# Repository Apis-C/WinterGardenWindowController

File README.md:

## Welcome to GitHub Pages

You can use the [editor on GitHub](https://github.com/Apis-C/WinterGardenWindowController/edit/master/README.md) to maintain and preview the content for your website in Markdown files.

Whenever you commit to this repository, GitHub Pages will run [Jekyll](https://jekyllrb.com/) to rebuild the pages in your site, from the content in your Markdown files.

### Markdown

Markdown is a lightweight and easy-to-use syntax for styling your writing. It includes conventions for

```markdown
Syntax highlighted code block

# Header 1
## Header 2
### Header 3

- Bulleted
- List

1. Numbered
2. List

**Bold** and _Italic_ and `Code` text

[Link](url) and 
```

For more details see [GitHub Flavored Markdown](https://guides.github.com/features/mastering-markdown/).

### Jekyll Themes

Your Pages site will use the layout and styles from the Jekyll theme you have selected in your [repository settings](https://github.com/Apis-C/WinterGardenWindowController/settings). The name of this theme is saved in the Jekyll `_config.yml` configuration file.

### Support or Contact

Having trouble with Pages? Check out our [documentation](https://help.github.com/categories/github-pages-basics/) or [contact support](https://github.com/contact) and we’ll help you sort it out.

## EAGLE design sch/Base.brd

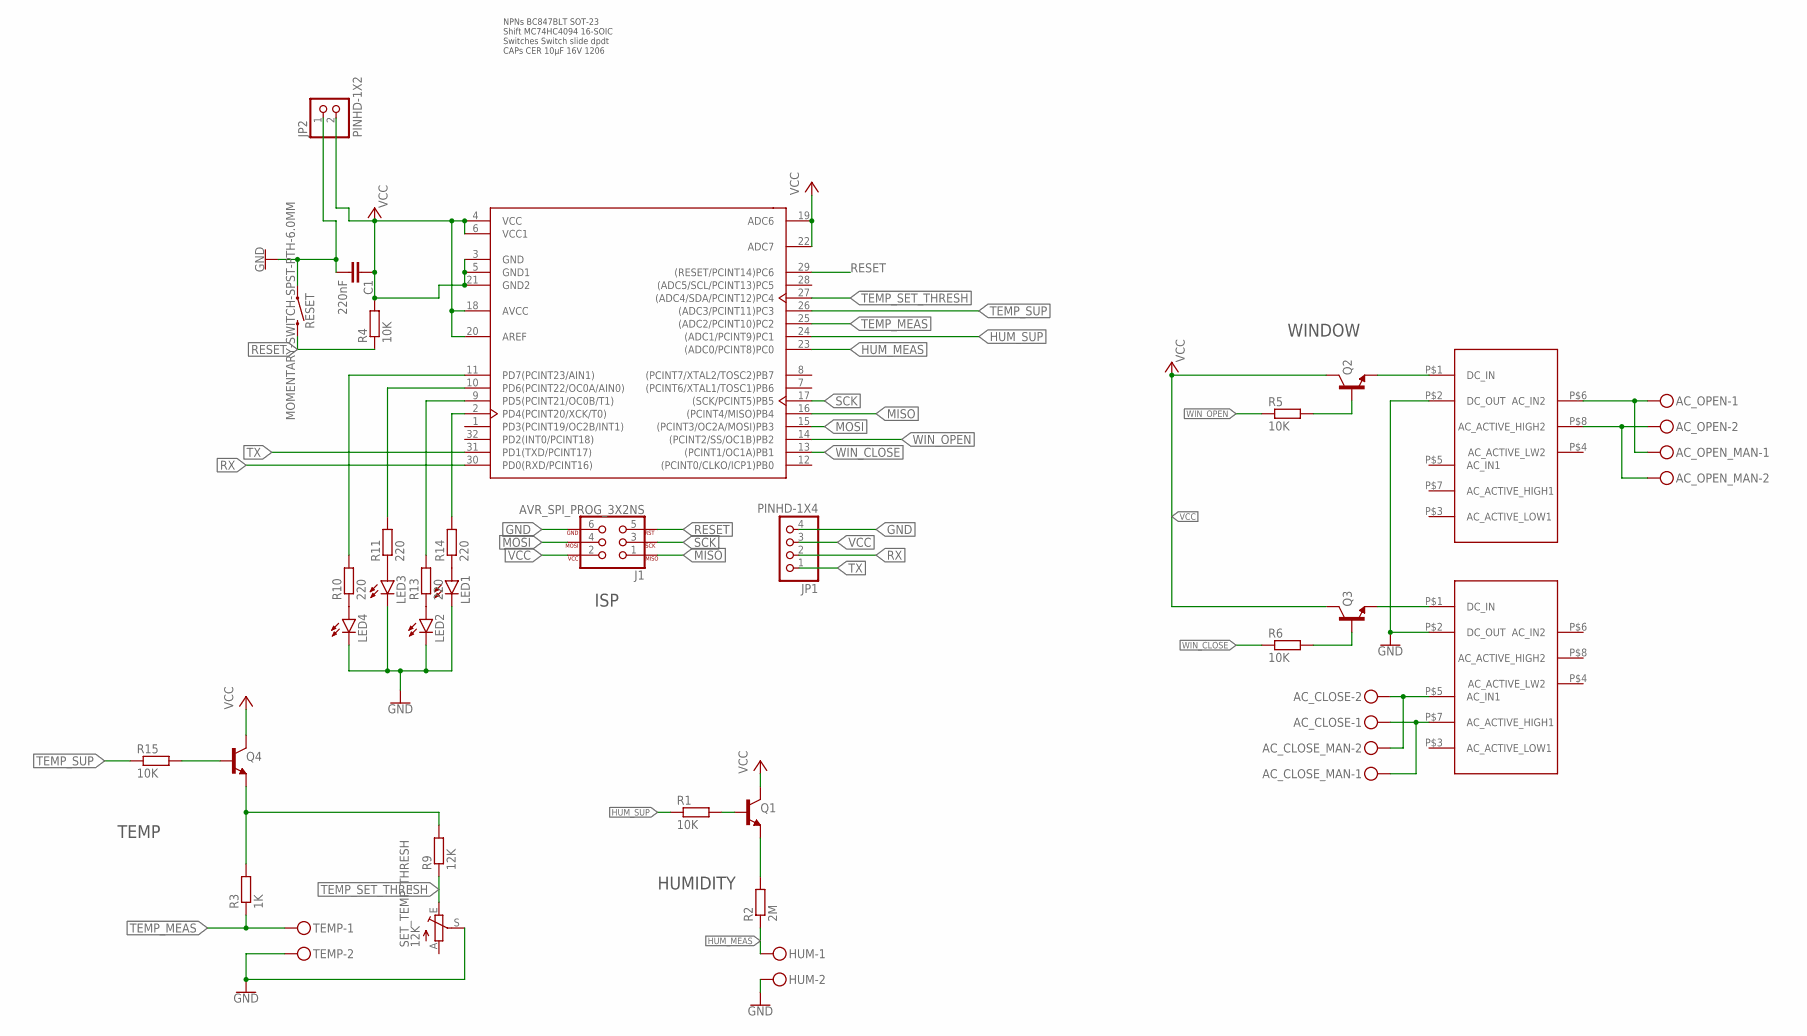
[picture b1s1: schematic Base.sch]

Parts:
AC_CLOSE: MKDSN1,5/2-5,08
AC_CLOSE_MAN: MKDSN1,5/2-5,08
AC_OPEN: MKDSN1,5/2-5,08
AC_OPEN_MAN: MKDSN1,5/2-5,08
C1: 220nF; C0805
HUM: MKDSN1,5/2-5,08
J1: AVR_SPI_PROG_3X2NS; 2X3-NS
JP1: PINHD-1X4; 1X04
JP2: PINHD-1X2; 1X02
LED1, LED2, LED3, LED4: LEDSMT1206; 1206
Q1, Q2, Q3, Q4: BD139; SOT23-BEC
R1, R4, R5, R6, R15: 10K; R1206
R2: 2M; R1206
R3: 1K; R1206
R9: 12K; R1206
R10, R11, R13, R14: 220; R1206
RESET: MOMENTARY-SWITCH-SPST-PTH-6.0MM; TACTILE_SWITCH_PTH_6.0MM
SET_TEMP_THRESH: 12K; LI15
TEMP: MKDSN1,5/2-5,08
U2: ATMEGA328P-AU; TQFP-32
U$1, U$2: RELAIS_EAG; REALAIS_EAG

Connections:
GND: C1.2, HUM.2, J1.6, JP1.4, JP2.1, LED1.C, LED2.C, LED3.C, LED4.C, RESET.1, SET_TEMP_THRESH.S, TEMP.2, U$1.P$2 (DC_OUT), U$2.P$2 (DC_OUT)
HUM_MEAS: HUM.1, R2.1, U2.23 ((ADC0/PCINT8)PC0)
HUM_SUP: R1.1, U2.24 ((ADC1/PCINT9)PC1)
MISO: J1.1, U2.16 ((PCINT4/MISO)PB4)
MOSI: J1.4, U2.15 ((PCINT3/OC2A/MOSI)PB3)
unnamed: Q1.B, R1.2
unnamed: Q1.E, R2.2
unnamed: AC_CLOSE.2, AC_CLOSE_MAN.2, U$2.P$5 (AC_IN1)
unnamed: Q2.E, U$1.P$1 (DC_IN)
unnamed: Q3.E, U$2.P$1 (DC_IN)
unnamed: AC_OPEN.2, AC_OPEN_MAN.2, U$1.P$8 (AC_ACTIVE_HIGH2)
unnamed: AC_OPEN.1, AC_OPEN_MAN.1, U$1.P$6 (AC_IN2)
unnamed: LED4.A, R10.1
unnamed: Q3.B, R6.2
unnamed: Q4.E, R3.2, R9.2
unnamed: LED3.A, R11.1
unnamed: AC_CLOSE.1, AC_CLOSE_MAN.1, U$2.P$7 (AC_ACTIVE_HIGH1)
unnamed: LED2.A, R13.1
unnamed: LED1.A, R14.1
unnamed: R14.2, U2.2 (PD4(PCINT20/XCK/T0))
unnamed: R13.2, U2.9 (PD5(PCINT21/OC0B/T1))
unnamed: R11.2, U2.10 (PD6(PCINT22/OC0A/AIN0))
unnamed: R10.2, U2.11 (PD7(PCINT23/AIN1))
RESET: J1.5, R4.1, RESET.3 (2), U2.29 ((RESET/PCINT14)PC6)
RX: JP1.2, U2.30 (PD0(RXD/PCINT16))
SCK: J1.3, U2.17 ((SCK/PCINT5)PB5)
TEMP_MEAS: R3.1, TEMP.1, U2.25 ((ADC2/PCINT10)PC2)
TEMP_SET_THRESH: R9.1, SET_TEMP_THRESH.E, U2.27 ((ADC4/SDA/PCINT12)PC4)
TEMP_SU: Q4.B, R15.2
TEMP_SUP: R15.1, U2.26 ((ADC3/PCINT11)PC3)
TX: JP1.1, U2.31 (PD1(TXD/PCINT17))
VCC: C1.1, J1.2, JP1.3, JP2.2, Q1.C, Q2.C, Q3.C, Q4.C, R4.2, U2.3 (GND), U2.4 (VCC), U2.5 (GND1), U2.6 (VCC1), U2.18 (AVCC), U2.19 (ADC6), U2.20 (AREF), U2.21 (GND2), U2.22 (ADC7)
WIN_CLOSE: R6.1, U2.13 ((PCINT1/OC1A)PB1)
WIN_O: Q2.B, R5.2
WIN_OPEN: R5.1, U2.14 ((PCINT2/SS/OC1B)PB2)

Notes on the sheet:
NPNs BC847BLT SOT-23 Shift MC74HC4094 16-SOIC Switches Switch slide dpdt CAPs CER 10µF 16V 1206
HUMIDITY
TEMP
ISP
WINDOW

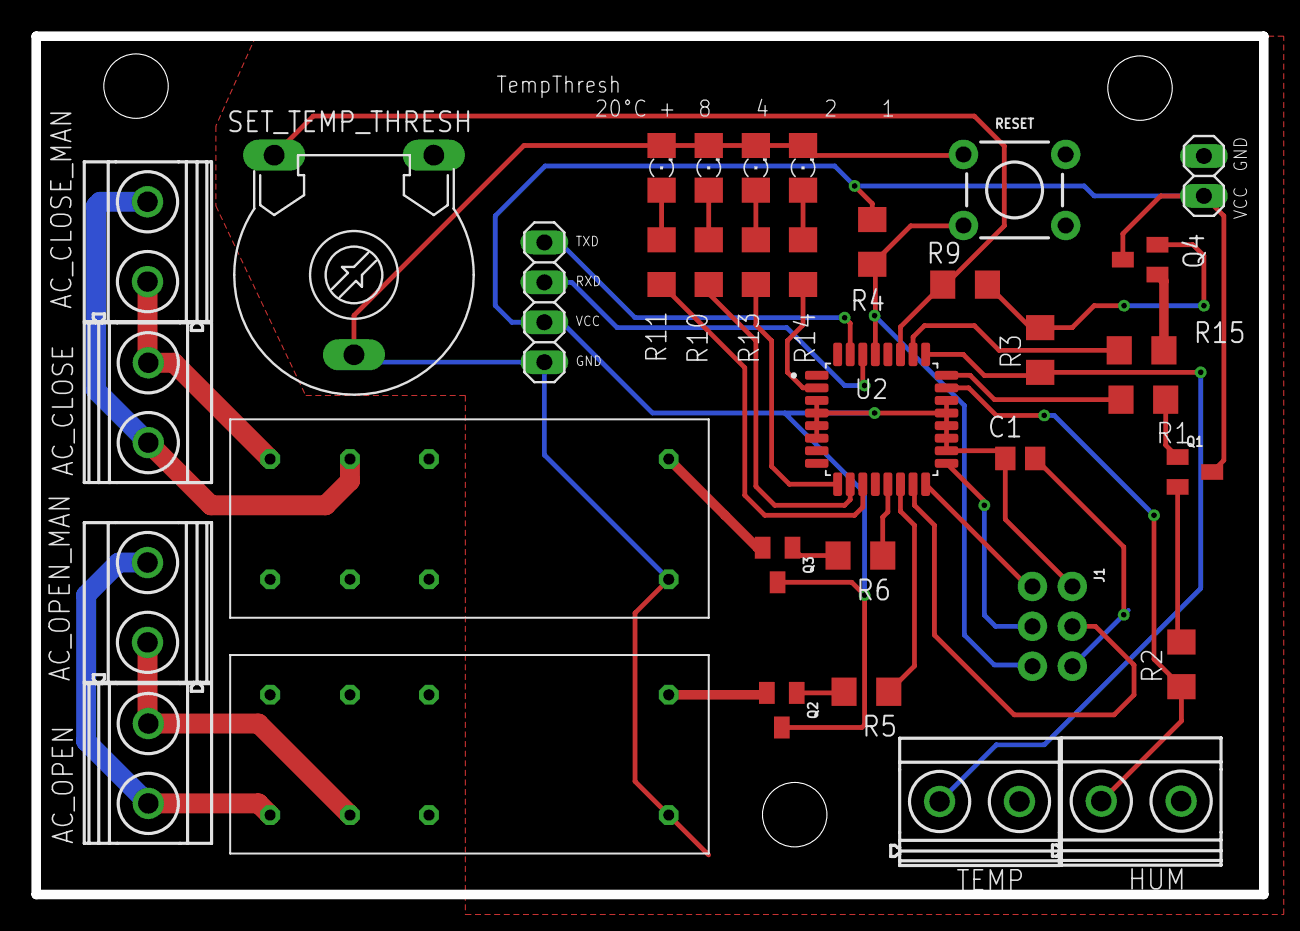
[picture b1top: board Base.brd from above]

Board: 2 copper layers, 78.1 x 54.6 mm, 35 parts (0 on the bottom side), 35 nets.

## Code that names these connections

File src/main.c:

/*
 * main.c
 *
 *  Created on: 18.06.2020
 *      @author: Bastian Teßin
 *      @brief This embedded code controlls the indoor-temprature and (outdoor-)rain based opening
 *      and closing of widows. The underlaying board is a Microchip ATMega328P. There is no communiction but the UART.
 */

#include <avr/io.h>
#include "lib/utils.h"
#include <stdlib.h>
#include <stdint.h>
#include <avr/interrupt.h>


void main(void)
{
	//Init LEDs
	DDRD |= ((1<<PD4) | (1<<PB5) | (1<<PD6) | (1<<PD7));

	//get hum manually
	//get temperature manually
	sei();
	while(1)
	{

	}
}

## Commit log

2020-06-22 Board ordered
2020-06-22 added zip and pdf
2020-06-22 Set theme jekyll-theme-midnight
2020-06-22 Untested ADC
2020-06-22 ADC untested II
2020-06-24 ADC ready to use UNTESTED: No Hardware available
2020-06-24 UART configured. UNTESTED: No hardware available
2020-06-24 Event-dispatcher
2020-06-24 not really important stuff

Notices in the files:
parts and their libraries:
SparkFun-Connectors: Licensing: Creative Commons ShareAlike 4.0 International - https://creativecommons.org/licenses/by-sa/4.0
